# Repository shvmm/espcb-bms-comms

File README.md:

# espcb-bms-comms
An ESP32 series based PCB facilitating BMS comms to Solar Inverters

# Features
1. Choice of CAN/~~RS485~~ for Inverter Communication
2. When using CAN, the choice is SN65HVD230 ~~or TJA1050/1051T~~
3. Three PCB variants based on: ESP32 DevKit, Seeed Studio XIAO S3, ~~or the S3-WROOM-1 module~~
4. Can be powered either by USB-C, ~~AC power supply, or LV Battery itself (mutually exclusive)~~
5. BMS connection through either UART, BLE ~~,CAN or RS485~~
6. Provision for 120Ohm Termination resistor jumper select
   
# References/Sources/Insights

0. https://github.com/Sleeper85/esphome-jk-bms-can
1. https://kicad-downloads.s3.cern.ch/index.html?prefix=windows/nightly/
2. https://github.com/syssi/esphome-jk-bms

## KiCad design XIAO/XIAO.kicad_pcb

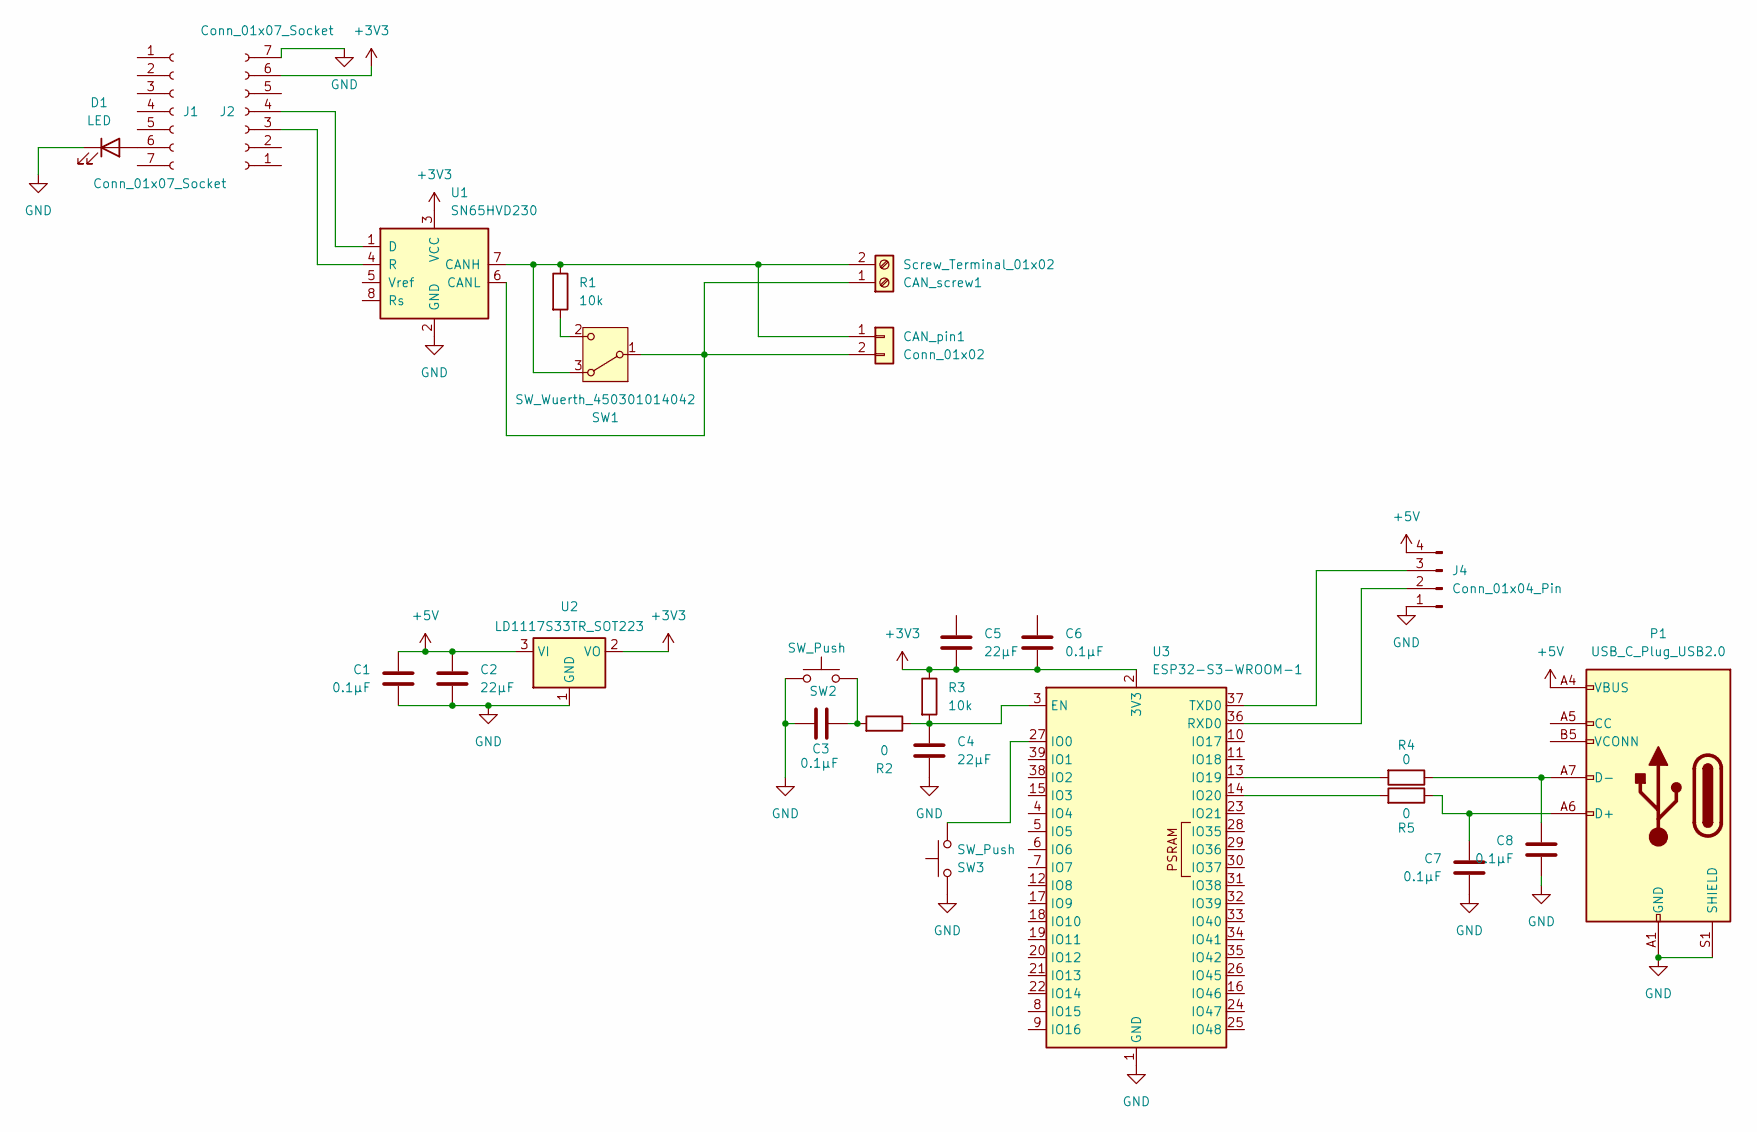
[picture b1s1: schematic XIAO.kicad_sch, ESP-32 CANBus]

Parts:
C1, C3, C6, C7, C8: 0.1μF; C_0805_2012Metric_Pad1.18x1.45mm_HandSolder
C2, C4, C5: 22μF; C_0805_2012Metric_Pad1.18x1.45mm_HandSolder
CAN_pin1: Conn_01x02; PinHeader_1x02_P2.54mm_Vertical
CAN_screw1: Screw_Terminal_01x02; TerminalBlock_Phoenix_MKDS-1,5-2-5.08_1x02_P5.08mm_Horizont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
D1: LED
J1, J2: Conn_01x07_Socket; PinSocket_1x07_P2.54mm_Vertical
J4: Conn_01x04_Pin; PinHeader_1x04_P2.54mm_Vertical
P1: USB_C_Plug_USB2.0; USB_C_Receptacle_GCT_USB4110
R1, R3: 10k; R_0805_2012Metric_Pad1.20x1.40mm_HandSolder
R2, R4, R5: 0; R_0805_2012Metric_Pad1.20x1.40mm_HandSolder
SW1: SW_Wuerth_450301014042; SW_Slide-03_Wuerth-WS-SLTV_10x2.5x6.4_P2.54mm
SW2, SW3: SW_Push; SW_Push_SPST_NO_Alps_SKRK
U1: SN65HVD230; SOIC-8_3.9x4.9mm_P1.27mm
U2: LD1117S33TR_SOT223; SOT-223-3_TabPin2
U3: ESP32-S3-WROOM-1

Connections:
+3V3: C5.2, C6.2, J2.6, R3.1, U1.3 (VCC), U2.2 (VO), U3.2 (3V3)
+5V: C1.1, C2.1, J4.4, P1.A4 (VBUS), P1.A9 (VBUS), P1.B4 (VBUS), P1.B9 (VBUS), U2.3 (VI)
GND: C1.2, C2.2, C3.1, C4.2, C7.2, C8.2, D1.1 (K), J2.7, J4.1, P1.A1 (GND), P1.A12 (GND), P1.B1 (GND), P1.B12 (GND), P1.S1 (SHIELD), SW2.1, SW3.1, U1.2 (GND), U2.1 (GND), U3.1 (GND), U3.40 (GND), U3.41 (GND)
unnamed: C3.2, R2.2, SW2.2
unnamed: CAN_pin1.1, CAN_screw1.2, R1.1, SW1.3 (A), U1.7 (CANH)
unnamed: CAN_pin1.2, CAN_screw1.1, SW1.1 (B), U1.6 (CANL)
unnamed: D1.2 (A), J1.6
unnamed: J2.3, U1.4 (R)
unnamed: J2.4, U1.1 (D)
unnamed: J4.2, U3.36 (RXD0)
unnamed: J4.3, U3.37 (TXD0)
unnamed: C7.1, P1.A6 (D+), R5.1
unnamed: C8.1, P1.A7 (D-), R4.1
unnamed: R1.2, SW1.2 (C)
unnamed: C4.1, R2.1, R3.2, U3.3 (EN)
unnamed: SW3.2, U3.27 (IO0)
unnamed: R4.2, U3.13 (IO19)
unnamed: R5.2, U3.14 (IO20)

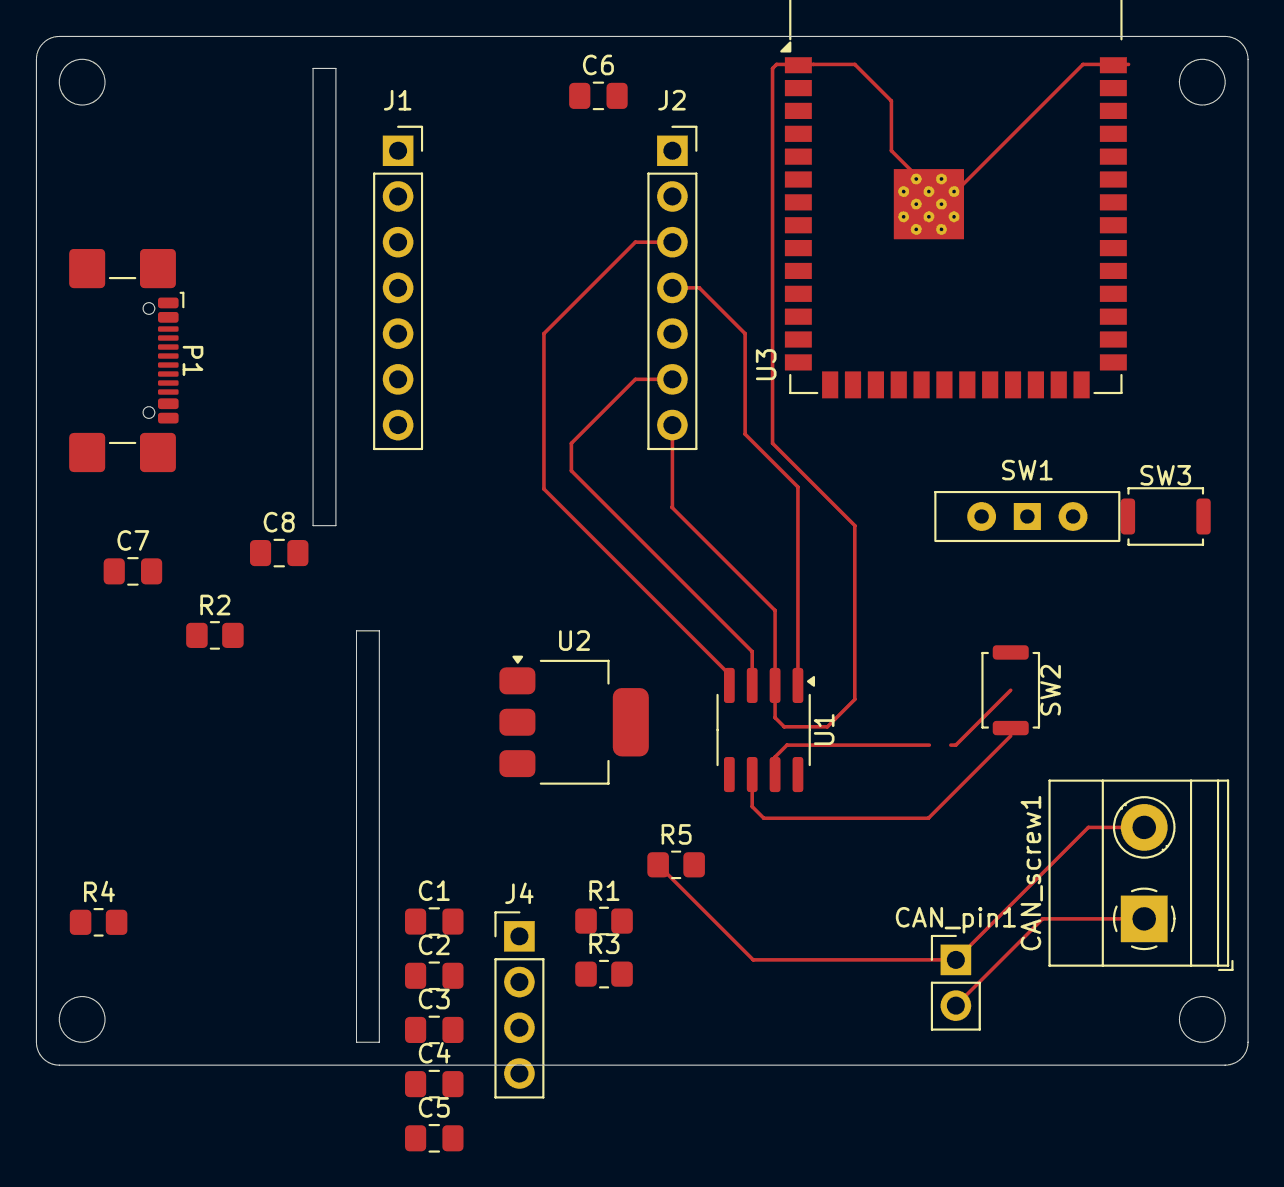
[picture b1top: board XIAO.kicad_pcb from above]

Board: 2 copper layers, 67.3 x 57.2 mm, 25 parts (0 on the bottom side), 17 nets.

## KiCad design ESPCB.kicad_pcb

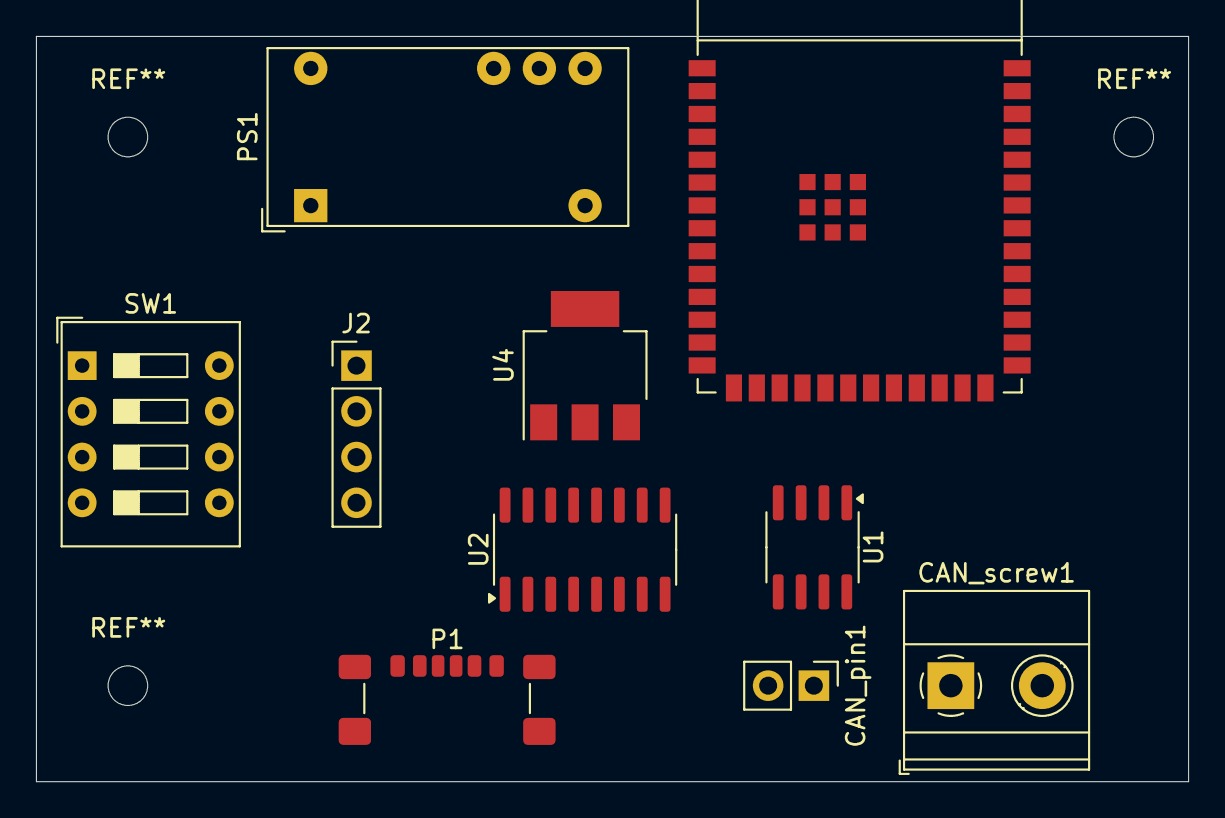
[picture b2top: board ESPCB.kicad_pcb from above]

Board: 11 copper layers, 64.0 x 41.4 mm, 10 parts (0 on the bottom side), 17 nets, no tracks yet.

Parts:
CAN_pin1: Conn_01x02; PinHeader_1x02_P2.54mm_Vertical
CAN_screw1: Screw_Terminal_01x02; TerminalBlock_Phoenix_MKDS-1,5-2-5.08_1x02_P5.08mm_Horizont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
J2: Conn_01x04; PinHeader_1x04_P2.54mm_Vertical
P1: USB_C_Plug_USB2.0; USB_C_Receptacle_GCT_USB4135-GF-A_6P_TopMnt_Horizontal
PS1: IH4805S; Converter_DCDC_XP_POWER-IHxxxxDH_THT
SW1: SW_DIP_x04; SW_DIP_SPSTx04_Slide_9.78x12.34mm_W7.62mm_P2.54mm
U1: SN65HVD230; SOIC-8_3.9x4.9mm_P1.27mm
U2: CH340C; SOIC-16_3.9x9.9mm_P1.27mm
U3: ESP32-S3-WROOM-1
U4: AMS1117-3.3; SOT-223-3_TabPin2

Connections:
GND: J2.3, P1.A12 (GND), P1.B12 (GND), U1.2 (GND), U2.1 (GND), U3.1 (GND), U3.15 (GND), U3.38 (GND), U3.39 (GND)
unnamed: CAN_pin1.1, CAN_screw1.1, U1.7 (CANH)
unnamed: CAN_pin1.2, CAN_screw1.2, U1.6 (CANL)
unnamed: J2.1, U3.27 (IO16)
unnamed: J2.2, U3.28 (IO17)
unnamed: J2.4, PS1.3 (+Vin)
unnamed: P1.B5 (VCONN), U4.3 (VI)
unnamed: U1.1 (D), U3.9 (IO33)
unnamed: U1.4 (R), U3.6 (IO34)
unnamed: U1.3 (VCC), U3.2 (VDD), U4.2 (VO)
unnamed: U2.3 (RXD), U3.34 (RXD0/IO3)
unnamed: U2.2 (TXD), U3.35 (TXD0/IO1)
unnamed: SW1.3, U3.20 (SCK/CLK)
unnamed: SW1.4, U3.19 (SCS/CMD)
unnamed: SW1.1, U3.17 (SHD/SD2)
unnamed: SW1.2, U3.18 (SWP/SD3)
VBUS: P1.A9 (VBUS), P1.B9 (VBUS), U2.16 (VCC)

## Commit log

2024-08-22 Update README.md
    First description
2024-08-22 prototype files
2024-08-22 prototype 3D render
2025-02-04 add in progress XIAO PCB
    The XIAO https://www.seeedstudio.com/xiao-series-page
    are tiny esp32 boards with battery charging IC built in making them extra useful for Solar applications.
